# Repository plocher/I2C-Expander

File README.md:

# I2C-9555
## License: CERN Open Hardware Licence v1.2

I2C PCF9555 / or / MCP23017 -based IO Expander with 4x IOB connections

This board can host either the MCP23017 or PCA9555 SO package chips.
The difference in proice is slight (~$0.50 or less), but the chips have slightly different programming and 
features, which may make one more desirable.  Rather than support 2x designs, it is easier to have one.

This is a 16-bit I/O board with 2x 8-bit ports: port0 and port1.

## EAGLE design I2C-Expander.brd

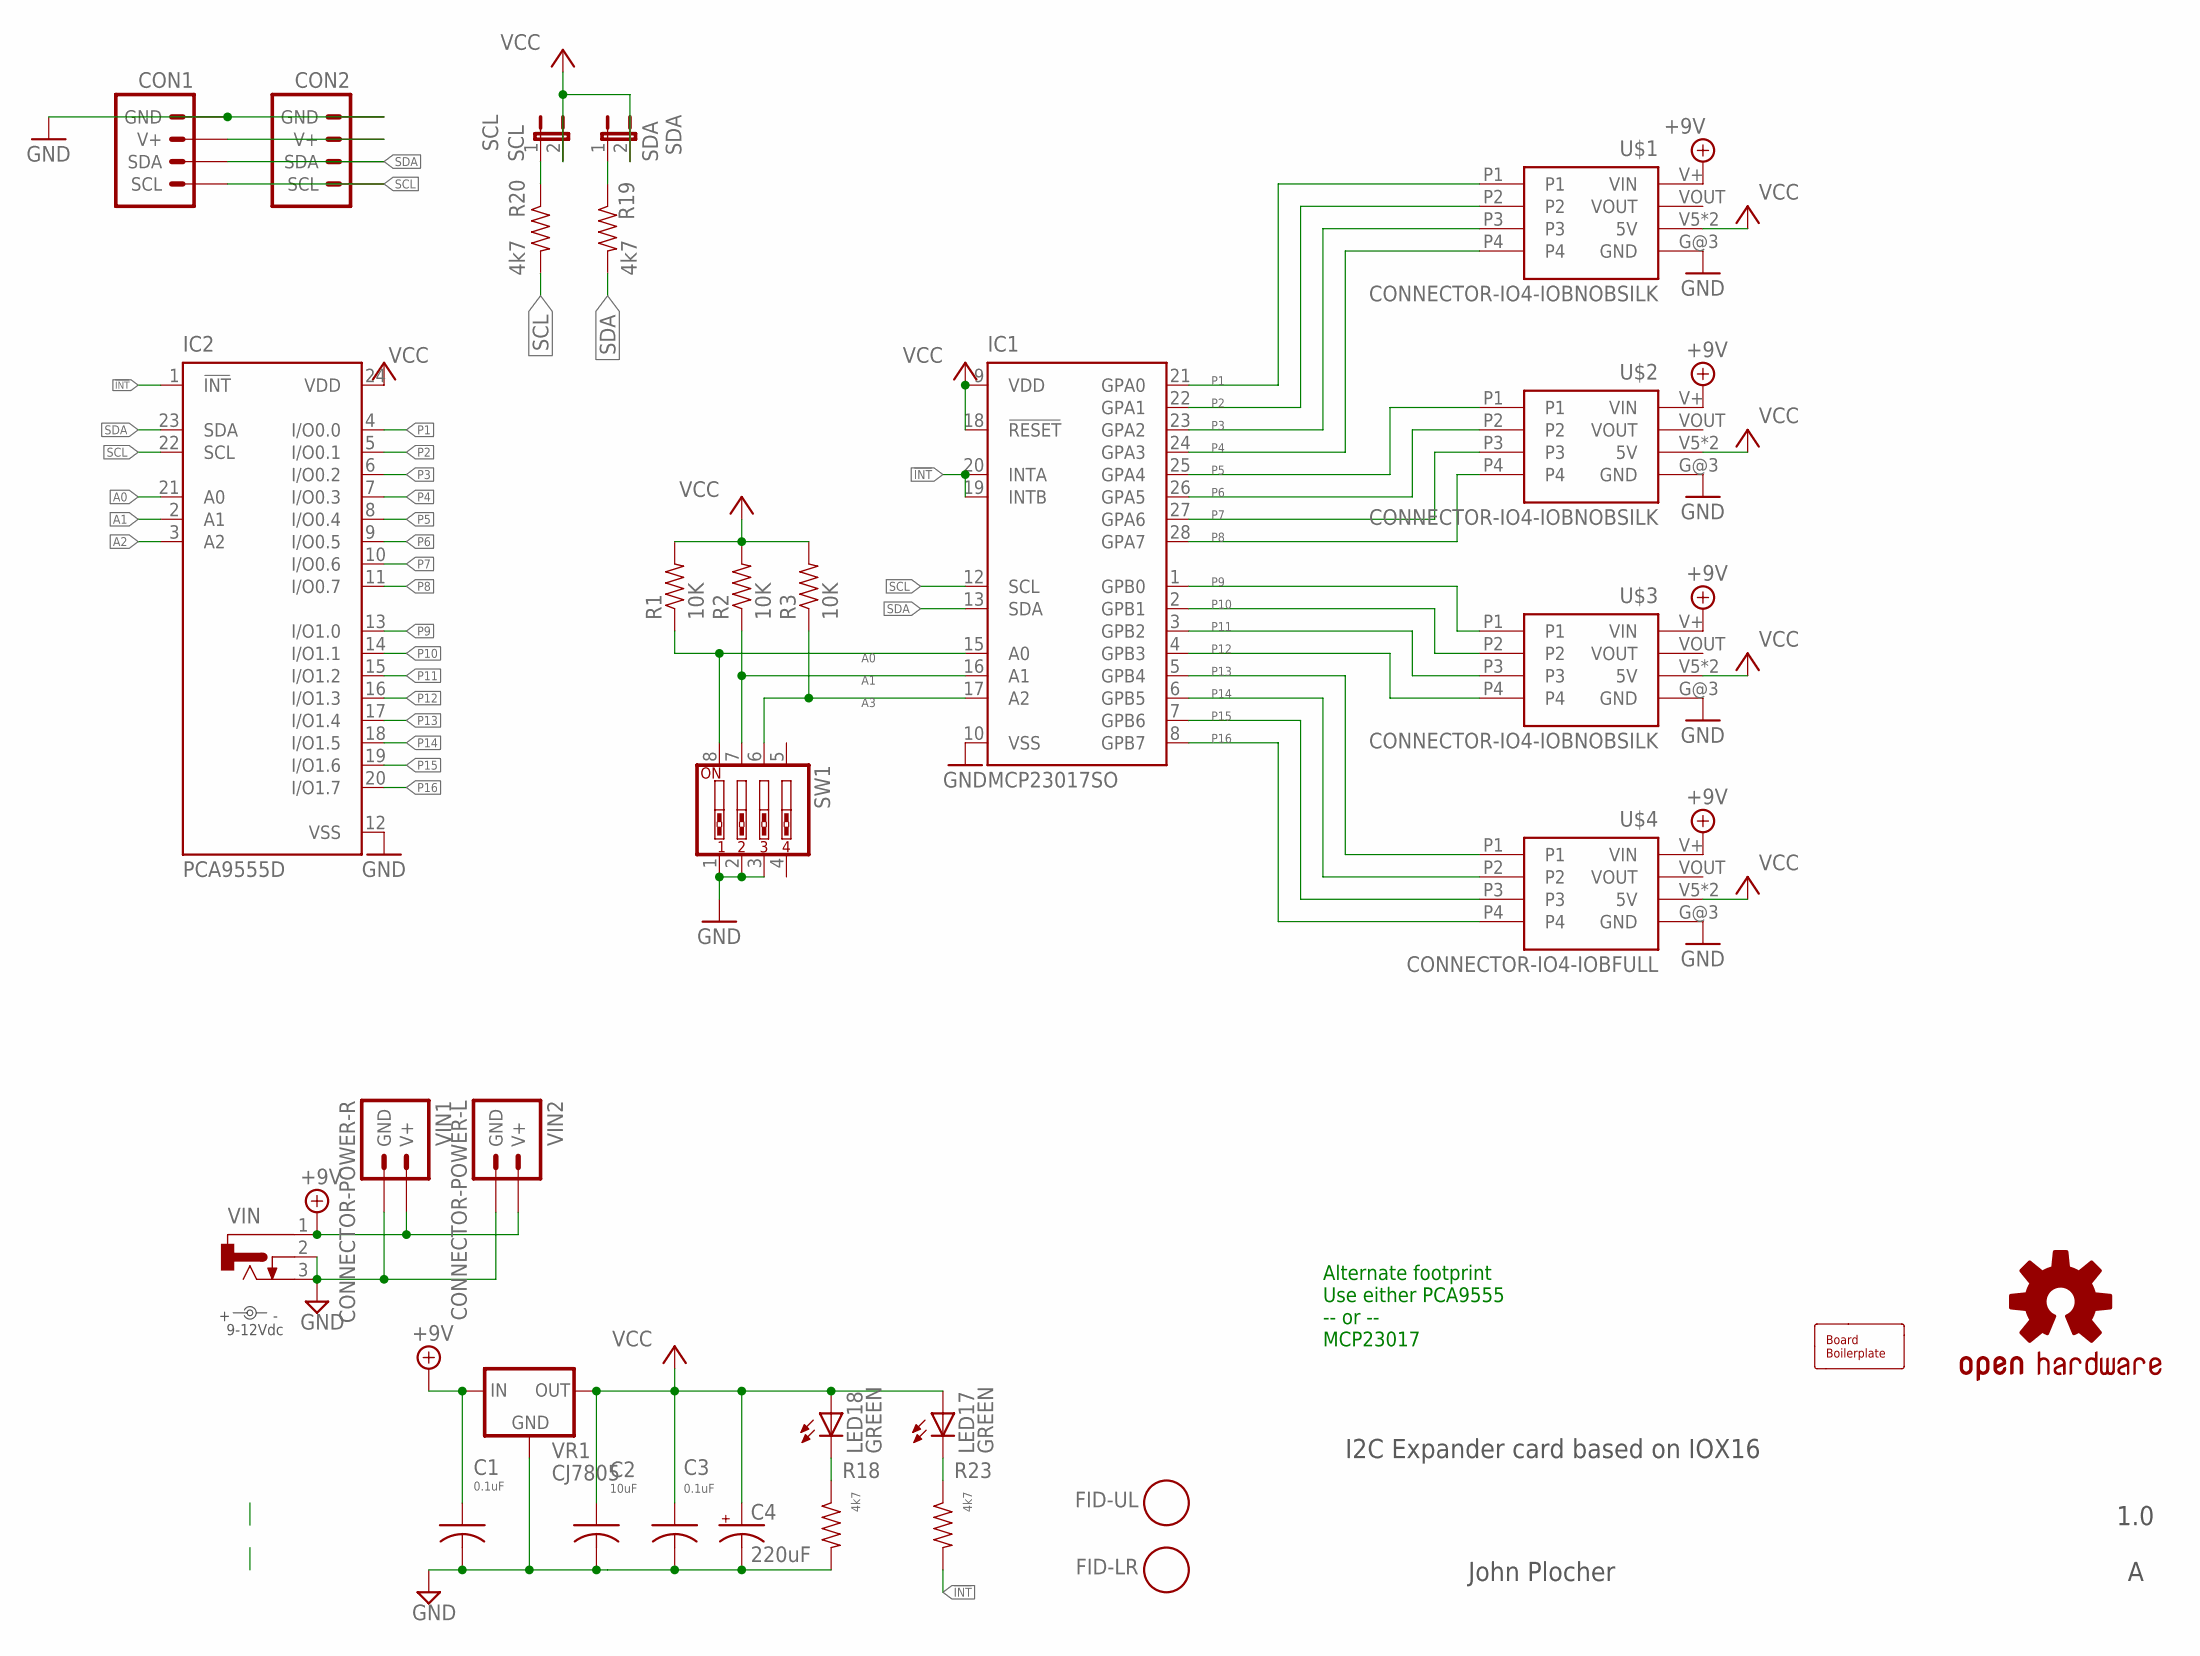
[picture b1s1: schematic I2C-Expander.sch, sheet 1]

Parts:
BOARD1: BOARD80X100-IOB; BOARD-DINRAIL-3.17IN-IOB
C1, C3: 0.1uF; 0805-CAP
C2: 10uF; 0805-CAP
C4: 220uF; 0810-CAP
CON1, CON2: CONNECTOR-I2CLEFT; I2C-L
FID-LR: FIDUCIAL; FIDUCIAL_1MM
FID-UL: FIDUCIAL; FIDUCIAL_1MM
IC1: MCP23017SO; SO28W
IC2: PCA9555D; SO24
LED17, LED18: GREEN; 0603-LED
OSHW1: DOC-OSHW-LOGO-M; OSHW-LOGO-M
POWER: 9-12Vdc; PWR_LABEL
R1, R2, R3: 10K; 0603-RES
R18, R19, R20, R23: 4k7; 0603-RES
SCL: SCL; 1X02_LOCK
SDA: SDA; 1X02_LOCK
SW1: SW_DIP-4; EDG-04
U$1, U$2, U$3: CONNECTOR-IO4-IOBNOBSILK; IOB-IO4-NOBOTSILK
U$4: CONNECTOR-IO4-IOBFULL; IO4-IOB
VIN: CONNECTOR-DC-POWER-RA; DCJ0202
VIN1: CONNECTOR-POWER-R; POWER-R
VIN2: CONNECTOR-POWER-L; POWER-R2
VR1: CJ7805; TO-252

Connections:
!INT: IC1.19 (INTB), IC1.20 (INTA), IC2.1 (!INT), R23.2
+9V: C1.1, U$1.V+ (VIN), U$2.V+ (VIN), U$3.V+ (VIN), U$4.V+ (VIN), VIN.1, VIN1.V+, VIN1.V+@1 (V+), VIN1.V+@2 (V+), VIN1.V+@3 (V+), VIN2.V+, VIN2.V+@1 (V+), VIN2.V+@2 (V+), VIN2.V+@3 (V+), VR1.1 (IN)
A0: IC1.15 (A0), IC2.21 (A0), R1.1, SW1.8
A1: IC1.16 (A1), IC2.2 (A1), R2.1, SW1.7
A2: IC2.3 (A2)
A3: IC1.17 (A2), R3.1, SW1.6
GND: C1.2, C2.2, C3.2, C4.-, CON1.GND, CON1.GND@1 (GND), CON2.GND, CON2.GND@1 (GND), IC1.10 (VSS), IC2.12 (VSS), R18.2, SW1.1, SW1.2, SW1.3, U$1.G@3 (GND), U$2.G@3 (GND), U$3.G@3 (GND), U$4.G@3 (GND), VIN.2, VIN.3, VIN1.GND, VIN1.GND@1 (GND), VIN1.GND@2 (GND), VIN1.GND@3 (GND), VIN2.GND, VIN2.GND@1 (GND), VIN2.GND@2 (GND), VIN2.GND@3 (GND), VR1.2 (GND); also elsewhere on the board
unnamed: CON1.V+, CON1.V+@1 (V+), CON2.V+, CON2.V+@1 (V+)
unnamed: LED17.C, R23.1
unnamed: R20.1, SCL.1
unnamed: R19.1, SDA.1
unnamed: LED18.C, R18.1
P1: IC1.21 (GPA0), IC2.4 (I/O0.0), U$1.P1; also elsewhere on the board
P2: IC1.22 (GPA1), IC2.5 (I/O0.1), U$1.P2; also elsewhere on the board
P3: IC1.23 (GPA2), IC2.6 (I/O0.2), U$1.P3; also elsewhere on the board
P4: IC1.24 (GPA3), IC2.7 (I/O0.3), U$1.P4; also elsewhere on the board
P5: IC1.25 (GPA4), IC2.8 (I/O0.4), U$2.P1; also elsewhere on the board
P6: IC1.26 (GPA5), IC2.9 (I/O0.5), U$2.P2; also elsewhere on the board
P7: IC1.27 (GPA6), IC2.10 (I/O0.6), U$2.P3; also elsewhere on the board
P8: IC1.28 (GPA7), IC2.11 (I/O0.7), U$2.P4; also elsewhere on the board
P9: IC1.1 (GPB0), IC2.13 (I/O1.0), U$3.P1; also elsewhere on the board
P10: IC1.2 (GPB1), IC2.14 (I/O1.1), U$3.P2; also elsewhere on the board
P11: IC1.3 (GPB2), IC2.15 (I/O1.2), U$3.P3; also elsewhere on the board
P12: IC1.4 (GPB3), IC2.16 (I/O1.3), U$3.P4; also elsewhere on the board
P13: IC1.5 (GPB4), IC2.17 (I/O1.4), U$4.P1; also elsewhere on the board
P14: IC1.6 (GPB5), IC2.18 (I/O1.5), U$4.P2; also elsewhere on the board
P15: IC1.7 (GPB6), IC2.19 (I/O1.6), U$4.P3; also elsewhere on the board
P16: IC1.8 (GPB7), IC2.20 (I/O1.7), U$4.P4; also elsewhere on the board
SCL: CON1.SCL, CON1.SCL@1 (SCL), CON2.SCL, CON2.SCL@1 (SCL), IC1.12 (SCL), IC2.22 (SCL), R20.2
SDA: CON1.SDA, CON1.SDA@1 (SDA), CON2.SDA, CON2.SDA@1 (SDA), IC1.13 (SDA), IC2.23 (SDA), R19.2
VCC: C2.1, C3.1, C4.+, IC1.9 (VDD), IC1.18 (!RESET), IC2.24 (VDD), LED17.A, LED18.A, R1.2, R2.2, R3.2, SCL.2, SDA.2, U$1.V5 (5V), U$1.V5@1 (5V), U$2.V5 (5V), U$2.V5@1 (5V), U$3.V5 (5V), U$3.V5@1 (5V), U$4.V5 (5V), U$4.V5@1 (5V), VR1.3 (OUT); also elsewhere on the board

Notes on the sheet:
I2C Expander card based on IOX16
1.0
John Plocher
Alternate footprint Use either PCA9555 -- or -- MCP23017

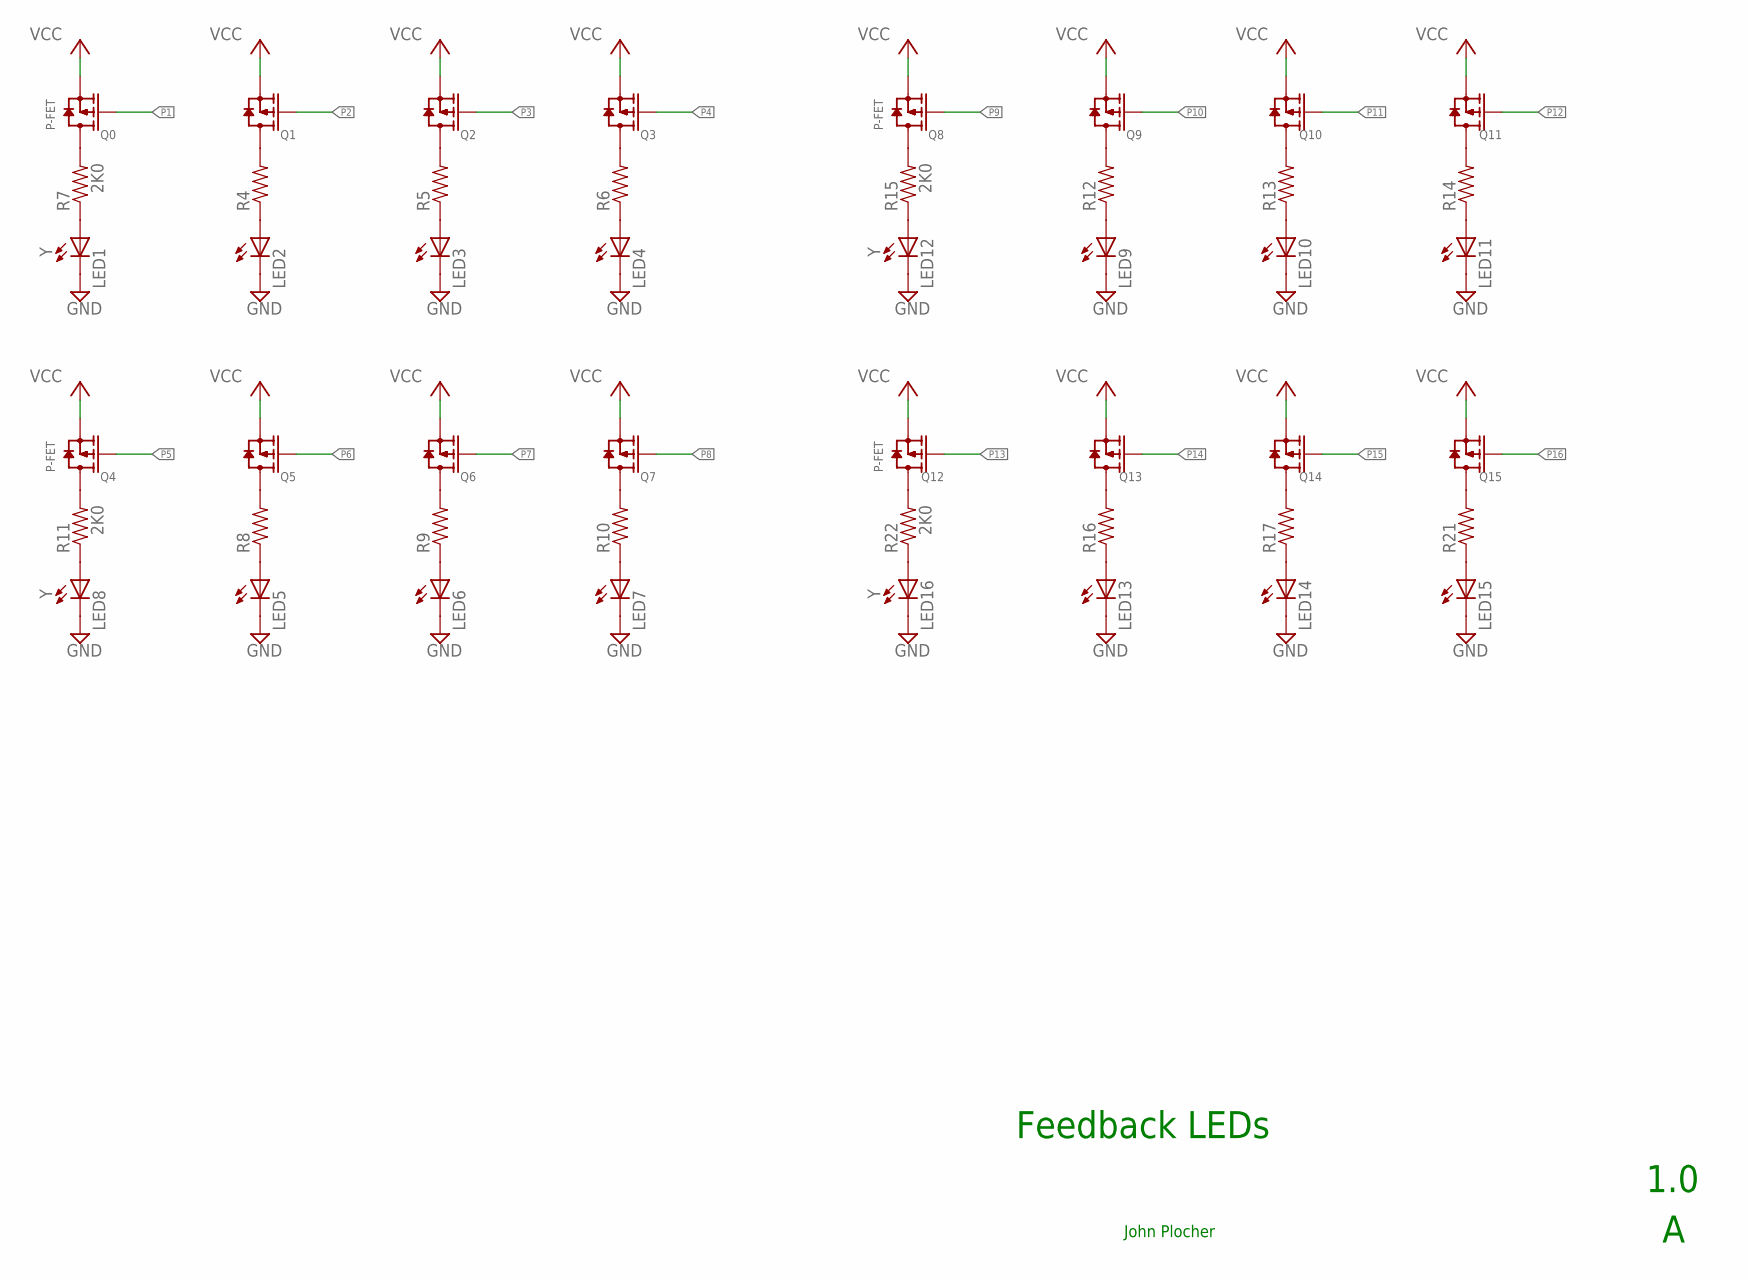
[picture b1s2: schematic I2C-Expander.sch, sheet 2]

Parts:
LED1, LED2, LED3, LED4, LED5, LED6, LED7, LED8, LED9, LED10, LED11, LED12, LED13, LED14, LED15, LED16: Y; 0603-LED
Q0, Q1, Q2, Q3, Q4, Q5, Q6, Q7, Q8, Q9, Q10, Q11, Q12, Q13, Q14, Q15: P-FET; SOT23
R4, R5, R6, R7, R8, R9, R10, R11, R12, R13, R14, R15, R16, R17, R21, R22: 2K0; 0805-RES

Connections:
GND: LED1.C, LED2.C, LED3.C, LED4.C, LED5.C, LED6.C, LED7.C, LED8.C, LED9.C, LED10.C, LED11.C, LED12.C, LED13.C, LED14.C, LED15.C, LED16.C; also elsewhere on the board
unnamed: Q4.3 (D), R11.2
unnamed: Q5.3 (D), R8.2
unnamed: Q6.3 (D), R9.2
unnamed: Q7.3 (D), R10.2
unnamed: LED8.A, R11.1
unnamed: LED5.A, R8.1
unnamed: LED6.A, R9.1
unnamed: LED7.A, R10.1
unnamed: Q8.3 (D), R15.2
unnamed: Q9.3 (D), R12.2
unnamed: Q10.3 (D), R13.2
unnamed: Q11.3 (D), R14.2
unnamed: LED12.A, R15.1
unnamed: LED9.A, R12.1
unnamed: LED10.A, R13.1
unnamed: LED11.A, R14.1
unnamed: Q12.3 (D), R22.2
unnamed: Q13.3 (D), R16.2
unnamed: Q14.3 (D), R17.2
unnamed: Q15.3 (D), R21.2
unnamed: LED16.A, R22.1
unnamed: LED13.A, R16.1
unnamed: LED14.A, R17.1
unnamed: LED15.A, R21.1
unnamed: Q0.3 (D), R7.2
unnamed: Q1.3 (D), R4.2
unnamed: Q2.3 (D), R5.2
unnamed: Q3.3 (D), R6.2
unnamed: LED1.A, R7.1
unnamed: LED2.A, R4.1
unnamed: LED3.A, R5.1
unnamed: LED4.A, R6.1
P1: Q0.1 (G); also elsewhere on the board
P2: Q1.1 (G); also elsewhere on the board
P3: Q2.1 (G); also elsewhere on the board
P4: Q3.1 (G); also elsewhere on the board
P5: Q4.1 (G); also elsewhere on the board
P6: Q5.1 (G); also elsewhere on the board
P7: Q6.1 (G); also elsewhere on the board
P8: Q7.1 (G); also elsewhere on the board
P9: Q8.1 (G); also elsewhere on the board
P10: Q9.1 (G); also elsewhere on the board
P11: Q10.1 (G); also elsewhere on the board
P12: Q11.1 (G); also elsewhere on the board
P13: Q12.1 (G); also elsewhere on the board
P14: Q13.1 (G); also elsewhere on the board
P15: Q14.1 (G); also elsewhere on the board
P16: Q15.1 (G); also elsewhere on the board
VCC: Q0.2 (S), Q1.2 (S), Q2.2 (S), Q3.2 (S), Q4.2 (S), Q5.2 (S), Q6.2 (S), Q7.2 (S), Q8.2 (S), Q9.2 (S), Q10.2 (S), Q11.2 (S), Q12.2 (S), Q13.2 (S), Q14.2 (S), Q15.2 (S); also elsewhere on the board

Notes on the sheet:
Feedback LEDs
1.0
John Plocher

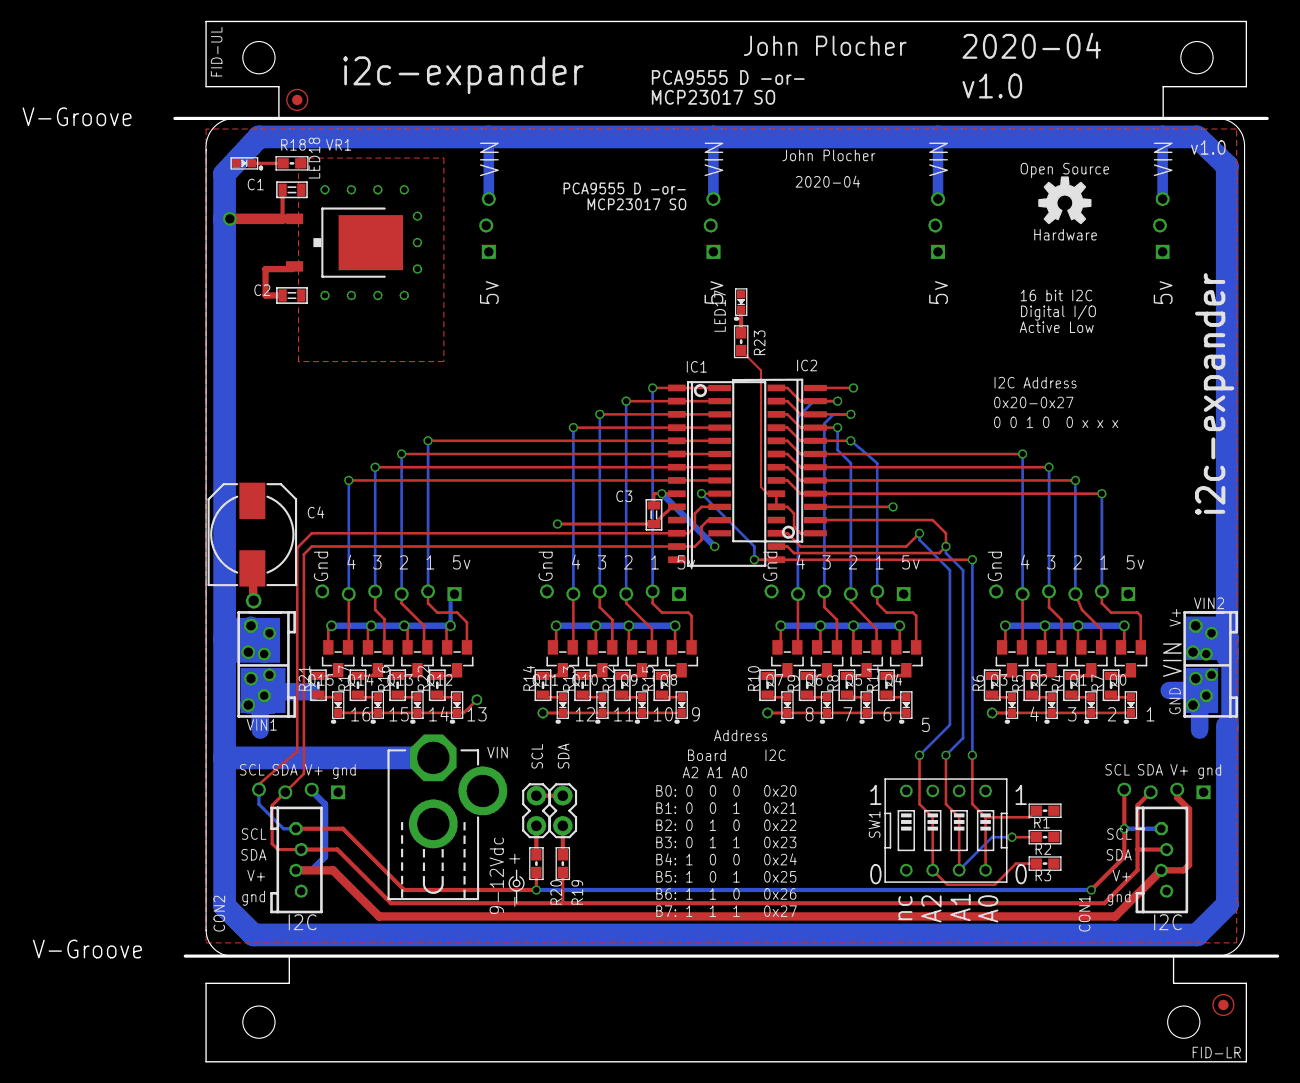
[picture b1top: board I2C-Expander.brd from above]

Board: 2 copper layers, 120.7 x 99.8 mm, 81 parts (0 on the bottom side), 62 nets.

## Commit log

2020-04-20 Initial version
2020-04-23 added LED on input changed interrupt pins
2020-05-04 updated tags
2020-08-05 fixed SPCoast lbr part orientation
2020-08-06 more silkscreen updates
2020-08-12 FID placement & names

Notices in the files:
parts and their libraries:
SPCoast: http://freedomdefined.org/OSHW Creative Commons - Attribution - ShareAlike 3.0
